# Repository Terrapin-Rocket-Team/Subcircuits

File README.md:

# Subcircuits

For more information on how to use this repository go to https://docs.google.com/document/d/1jy8WAUwOLDJCLKDHjfdK5C19-00sSEa3fJpSzj2nrzQ/edit#heading=h.e6dmhkmb6wxf

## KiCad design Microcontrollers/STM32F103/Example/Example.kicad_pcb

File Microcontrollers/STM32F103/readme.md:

# STM32F103 Status: TESTED
This is a subcircuit which contains all of the components required for a STM32F103 to function, except for power regulation. It will require a steady 3.3v source of power. The 10 pin JTAG connector has been tested with a Segger J-Link programming cable. Allows for debugging over SWD without any additional configuration. This also provides an I2C bus, but it does not provide an SPI bus yet.

## Components:

- C1-C6: Any ceramic capacitor with the correct capacitance and a voltage rating of at least 3.3v
- J1: [10 pin JTAG Connector](https://www.digikey.com/en/products/detail/samtec-inc./FTSH-105-01-H-DV-K-P-TR/9594223)
- R1-R3: Any resistor with the correct resistance. 
- U1: [STM32F103](https://www.digikey.com/en/products/detail/stmicroelectronics/STM32F103C8T6/1646338)
- Y1: [Resonator. Linked part is 10MhZ, but 8MhZ is preferred](https://www.digikey.com/en/products/detail/murata-electronics/CSTNE10M0G550000R0/8747719)

## Considerations
- Make sure C3-C6 are placed as close to the pins they connect to as possible
- C1 isn't as important to position closely
- Resonator is optional. If you are using USB without an intermediary chip, use an 8MhZ resonator

## Recommended Routing:

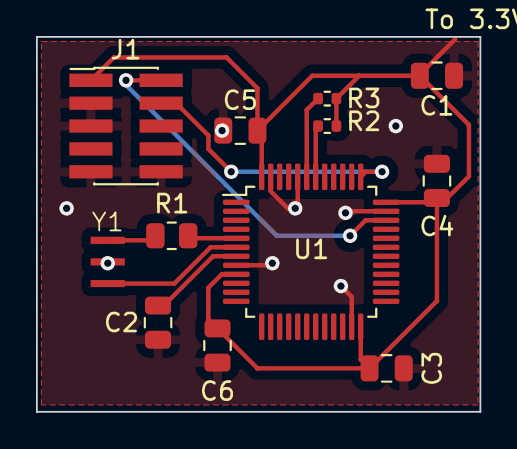
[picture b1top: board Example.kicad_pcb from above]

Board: 2 copper layers, 24.6 x 20.8 mm, 12 parts (0 on the bottom side), 10 nets.

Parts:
C1: 4.7uF; C_0805_2012Metric
C2, C3, C4, C5, C6: 100nF; C_0805_2012Metric
J1: Conn_ARM_JTAG_SWD_10; PinHeader_2x05_P1.27mm_Vertical_SMD
R1: 1M; R_0805_2012Metric
R2, R3: 4.7k; R_0402_1005Metric
U1: STM32F103C8Tx; LQFP-48_7x7mm_P0.5mm
Y1: Resonator; JGC42-8828A_CSTNE10M0G550000R0

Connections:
+3V3: C1.2, C3.2, C4.2, C5.2, C6.2, J1.1 (VTref), R2.2, R3.2, U1.9 (VDDA), U1.24 (VDD), U1.36 (VDD), U1.48 (VDD)
/mcu/SCL: R2.1, U1.42 (PB6)
/mcu/SDA: R3.1, U1.43 (PB7)
/mcu/SWCLK: J1.4 (SWDCLK/TCK), U1.37 (PA14)
/mcu/SWDIO: J1.2 (SWDIO/TMS), U1.34 (PA13)
GND: C1.1, C2.2, C3.1, C4.1, C5.1, C6.1, J1.3 (GND), J1.5 (GND), J1.9 (GNDDetect), J1.10 (~RESET), U1.8 (VSSA), U1.23 (VSS), U1.35 (VSS), U1.44 (BOOT0), U1.47 (VSS), Y1.2
unnamed: R1.2, Y1.1
unnamed: C2.1, U1.7 (NRST)
unnamed: R1.1, U1.5 (PD0)
unnamed: U1.6 (PD1), Y1.3

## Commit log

2023-07-25 Added power regulation circuit
2023-07-25 Added LPS22HB subcircuit
2023-07-25 Added STM32F103
2023-07-25 Added status to readmes
2023-07-25 Renamed power subcircuit to follow new convention
2023-07-27 Added 18v-5v regulator circuit
2023-09-16 add flip flop circuit
2023-09-16 added testing video
2023-09-22 Added components for BMP388 LSM9DS1
2023-09-22 Removed unneeded folder
2023-09-27 Finished schematic draft
    Completed connections for schematic
2023-10-11 Symbol Change
    Had to change outline of BMP and LSM to F.courtyard instead of Edge.Cut so that connections could be made.
2023-10-14 Updated BMP and LSM Files
    Added silk screen lines
2023-10-17 Updated Sensor Footprints
    Updated board pad/hole sizes
